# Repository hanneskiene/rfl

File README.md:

# rfl
4ch RC receiver/transmitter with switched diversity antennas to retrofit 35MHz remotes.

- PPM input on CH3 to connect to old 35MHz internal PPM signal
- Dual U.fl connectors for antennas (single transmit, dual receive)
- 4 PWM outputs (3.3V)
- USB-C for programming 

## Parts
- SX1281 2.4GHz Transceiver IC
- SE2431L LNA/PA with up to +24 dBm
- STM32G0B1KET6N MCU
- TPS7A19 with up to 40V Vin

## Assembly
QFN parts need a reflow oven/hot air station, the rest is 0402 or larger.

## Fimware
First prototype implementation with fixed frequency hopping table, very simple Rx-antenna diversity is "useable". The firmware currently checks for a valid PPM input if thats not found switches to receiver mode.

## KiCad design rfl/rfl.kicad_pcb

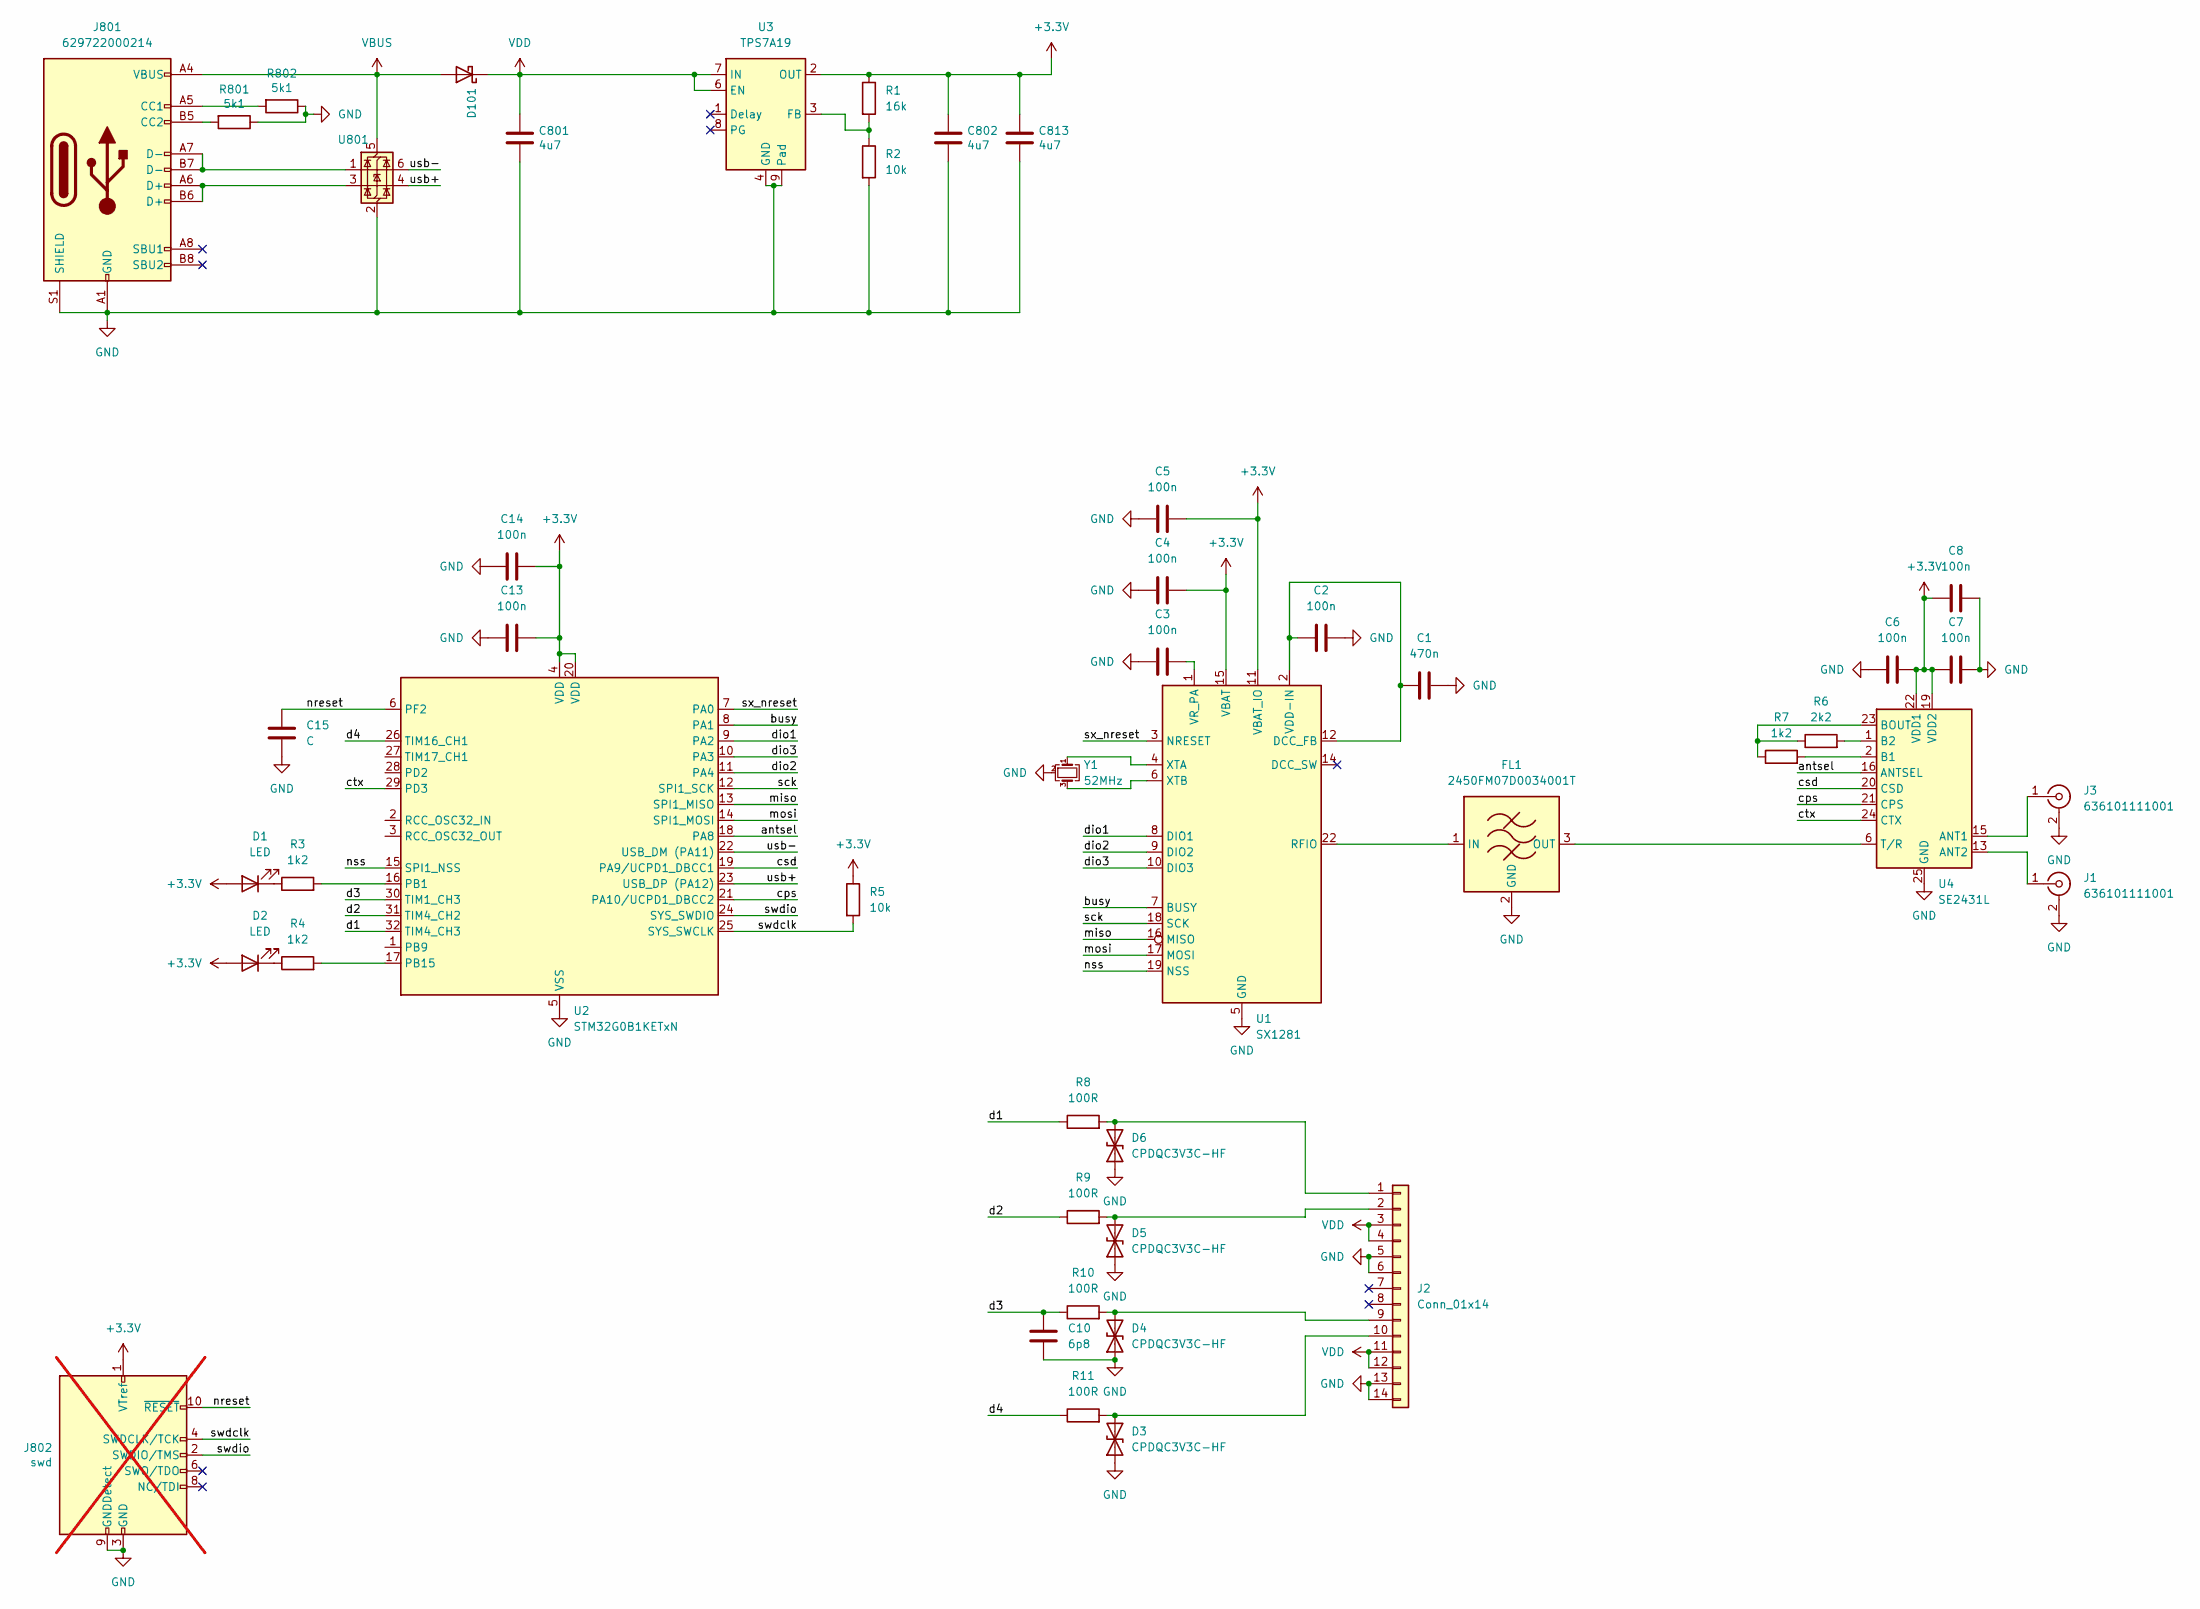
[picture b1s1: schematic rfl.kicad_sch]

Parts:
C1: 470n; C_0603_1608Metric
C2, C3, C4, C5, C6, C7, C13, C14: 100n; C_0402_1005Metric
C8: 100n; C_0603_1608Metric
C10: 6p8; C_0402_1005Metric
C15: C; C_0402_1005Metric
C801, C802, C813: 4u7; C_1206_3216Metric; Rating >=50V, X7R
D1, D2: LED; LED_0402_1005Metric
D3, D4, D5, D6: CPDQC3V3C-HF; D_0402_1005Metric
D101: D_SMF; PartNo V3FL45HM3/H
FL1: 2450FM07D0034001T
J1, J3: 636101111001; U.FL_Hirose_U.FL-R-SMT-1_Vertical
J2: Conn_01x14; PinHeader_2x07_P2.54mm_Edge; PartNo 61301421121
J801: 629722000214; USB_C_Receptacle_GCT_USB4105-xx-A_16P_TopMnt_Horizontal; PartNo USB4105-GF-A
J802: swd; PinHeader_2x05_P1.27mm_Vertical_SMD; PartNo e.g. FTSH-105-01-L-DV-K; not fitted
R1: 16k; R_0402_1005Metric
R2, R5: 10k; R_0402_1005Metric
R3, R4, R7: 1k2; R_0402_1005Metric
R6: 2k2; R_0402_1005Metric
R8, R9, R10, R11: 100R; R_0402_1005Metric
R801, R802: 5k1; R_0402_1005Metric
U1: SX1281; QFN-24-1EP_4x4mm_P0.5mm_EP2.6x2.6mm
U2: STM32G0B1KETxN; LQFP-32_7x7mm_P0.8mm
U3: TPS7A19; VSON-8-1EP_3x3mm_P0.65mm_EP1.65x2.4mm
U4: SE2431L; QFN-24-1EP_3x4mm_P0.4mm_EP1.65x2.65mm
U801: USBLC6-2SC6; SOT-23-6; PartNo USBLC6-2SC6
Y1: 52MHz; Crystal_SMD_2016-4Pin_2.0x1.6mm; PartNo NX2016SA-52.000000MHZ

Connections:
+3.3V: C4.2, C5.2, C6.2, C7.1, C8.1, C13.2, C14.2, C802.1, C813.1, D1.2 (A), D2.2 (A), J802.1 (VTref), R1.1, R5.1, U1.11 (VBAT_IO), U1.15 (VBAT), U2.4 (VDD), U2.20 (VDD), U3.2 (OUT), U4.19 (VDD2), U4.22 (VDD1)
/antsel: U2.18 (PA8), U4.16 (ANTSEL)
/busy: U1.7 (BUSY), U2.8 (PA1)
/cps: U2.21 (PA10/UCPD1_DBCC2), U4.21 (CPS)
/csd: U2.19 (PA9/UCPD1_DBCC1), U4.20 (CSD)
/ctx: U2.29 (PD3), U4.24 (CTX)
/d1: R8.1, U2.32 (TIM4_CH3)
/d2: R9.1, U2.31 (TIM4_CH2)
/d3: C10.2, R10.1, U2.30 (TIM1_CH3)
/d4: R11.1, U2.26 (TIM16_CH1)
/dio1: U1.8 (DIO1), U2.9 (PA2)
/dio2: U1.9 (DIO2), U2.11 (PA4)
/dio3: U1.10 (DIO3), U2.10 (PA3)
/miso: U1.16 (MISO), U2.13 (SPI1_MISO)
/mosi: U1.17 (MOSI), U2.14 (SPI1_MOSI)
/nreset: C15.2, J802.10 (~RESET), U2.6 (PF2)
/nss: U1.19 (NSS), U2.15 (SPI1_NSS)
/sck: U1.18 (SCK), U2.12 (SPI1_SCK)
/swdclk: J802.4 (SWDCLK/TCK), R5.2, U2.25 (SYS_SWCLK)
/swdio: J802.2 (SWDIO/TMS), U2.24 (SYS_SWDIO)
/sx_nreset: U1.3 (NRESET), U2.7 (PA0)
/usb+: U2.23 (USB_DP (PA12)), U801.4 (I/O2)
/usb-: U2.22 (USB_DM (PA11)), U801.6 (I/O1)
GND: C1.2, C2.2, C3.1, C4.1, C5.1, C6.1, C7.2, C8.2, C10.1, C13.1, C14.1, C15.1, C801.2, C802.2, C813.2, D3.1 (A1), D4.1 (A1), D5.1 (A1), D6.1 (A1), FL1.2 (GND), FL1.4 (GND), J1.2 (Ext), J2.5, J2.6, J2.13, J2.14, J3.2 (Ext), J801.A1 (GND), J801.A12 (GND), J801.B1 (GND), J801.B12 (GND), J801.S1 (SHIELD), J802.3 (GND), J802.5 (GND), J802.9 (GNDDetect), R2.2, R801.1, R802.1, U1.5 (GND), U1.13 (GND), U1.20 (GND), U1.21 (GND), U1.23 (GND), U1.24 (GND), U1.25 (GND), U2.5 (VSS), U3.4 (GND), U3.5 (GND), U3.9 (Pad), U4.9 (GND), U4.10 (GND), U4.11 (GND), U4.12 (GND), U4.14 (GND), U4.18 (GND), U4.25 (GND), U801.2 (GND), Y1.2 (G), Y1.4 (G)
unnamed: D1.1 (K), R3.1
unnamed: D2.1 (K), R4.1
unnamed: D3.2 (A2), J2.10, R11.2
unnamed: D4.2 (A2), J2.9, R10.2
unnamed: D5.2 (A2), J2.2, R9.2
unnamed: D6.2 (A2), J2.1, R8.2
unnamed: FL1.1 (IN), U1.22 (RFIO)
unnamed: FL1.3 (OUT), U4.6 (T/R)
unnamed: J1.1 (In), U4.13 (ANT2)
unnamed: J3.1 (In), U4.15 (ANT1)
unnamed: J801.A5 (CC1), R802.2
unnamed: J801.B5 (CC2), R801.2
unnamed: J801.A6 (D+), J801.B6 (D+), U801.3 (I/O2)
unnamed: J801.A7 (D-), J801.B7 (D-), U801.1 (I/O1)
unnamed: C1.1, C2.1, U1.2 (VDD-IN), U1.12 (DCC_FB)
unnamed: C3.2, U1.1 (VR_PA)
unnamed: U1.4 (XTA), Y1.1
unnamed: U1.6 (XTB), Y1.3
unnamed: R3.2, U2.16 (PB1)
unnamed: R4.2, U2.17 (PB15)
unnamed: R1.2, R2.1, U3.3 (FB)
unnamed: R7.2, U4.2 (B1)
unnamed: R6.2, U4.1 (B2)
unnamed: R6.1, R7.1, U4.23 (BOUT)
VBUS: D101.2 (A), J801.A4 (VBUS), J801.A9 (VBUS), J801.B4 (VBUS), J801.B9 (VBUS), U801.5 (VBUS)
VDD: C801.1, D101.1 (K), J2.3, J2.4, J2.11, J2.12, U3.6 (EN), U3.7 (IN)

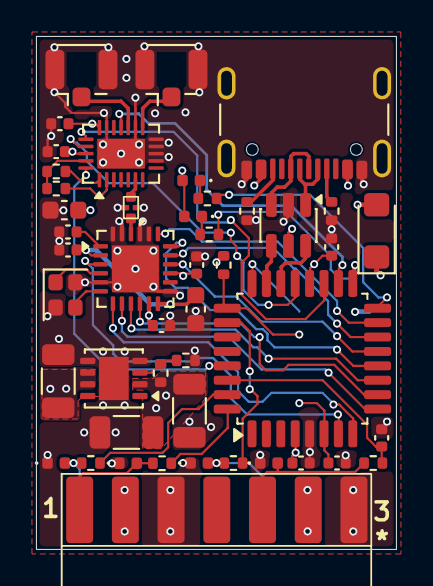
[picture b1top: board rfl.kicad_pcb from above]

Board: 4 copper layers, 20.0 x 28.5 mm, 47 parts (1 on the bottom side), 50 nets.

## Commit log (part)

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2026-04-18 readme
2026-05-30 before switch
2026-05-30 v2 with rf switch wip
2026-05-30 more files
2026-05-30 updated image
2026-05-31 cleaned up layout
2026-05-31 fixed edge cleareance
2026-06-16 first firmware version that transmits
2026-06-17 very simple frequency hopping
2026-06-21 first working rec/send rc
2026-06-28 Added watchdog
